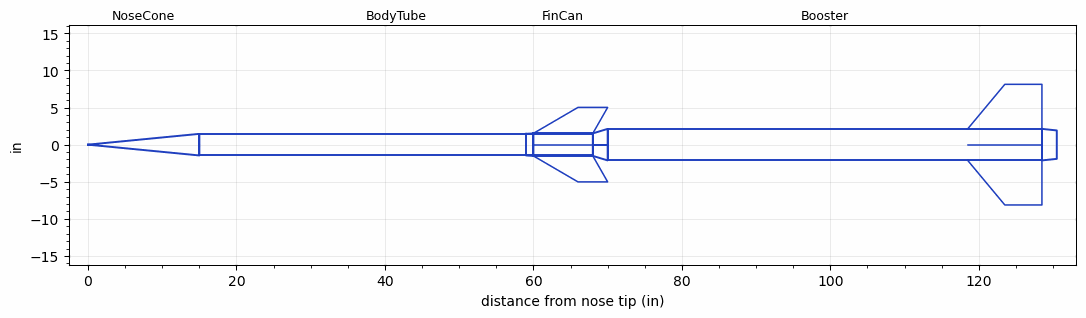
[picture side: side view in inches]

<RASAeroDocument>
 <FileVersion>2</FileVersion>
 <RocketDesign>
  <NoseCone>
   <Length>15</Length>
   <Diameter>2.91</Diameter>
   <Shape>Conical</Shape>
   <BluntRadius>0.1</BluntRadius>
   <Location>0</Location>
  </NoseCone>
  <BodyTube>
   <Length>53</Length>
   <Diameter>2.91</Diameter>
   <Location>15</Location>
   <Protuberance>
    <StreamlinedNoBaseDrag>0</StreamlinedNoBaseDrag>
    <StreamlinedWithBaseDrag>0.65</StreamlinedWithBaseDrag>
    <InclinedPlate1Angle>0</InclinedPlate1Angle>
    <InclinedPlate1FrontalArea>0</InclinedPlate1FrontalArea>
    <InclinedPlate2Angle>0</InclinedPlate2Angle>
    <InclinedPlate2FrontalArea>0</InclinedPlate2FrontalArea>
   </Protuberance>
  </BodyTube>
  <FinCan>
   <Length>8</Length>
   <Diameter>3.035</Diameter>
   <InsideDiameter>2.91</InsideDiameter>
   <Location>68</Location>
   <ShoulderLength>1</ShoulderLength>
   <Offset>-8</Offset>
   <Fin>
    <Count>4</Count>
    <Chord>8</Chord>
    <Span>3.5</Span>
    <SweepDistance>6</SweepDistance>
    <TipChord>4</TipChord>
    <Thickness>0.187</Thickness>
    <LERadius>0.01</LERadius>
    <Location>8</Location>
    <AirfoilSection>Hexagonal</AirfoilSection>
    <FX1>0.75</FX1>
    <FX3>0.75</FX3>
   </Fin>
  </FinCan>
  <Booster>
   <Length>58.5</Length>
   <Diameter>4.25</Diameter>
   <InsideDiameter>3.035</InsideDiameter>
   <RailGuideDiameter>0.7</RailGuideDiameter>
   <RailGuideHeight>0.6</RailGuideHeight>
   <Location>68</Location>
   <ShoulderLength>2</ShoulderLength>
   <BoattailLength>2</BoattailLength>
   <BoattailRearDiameter>3.828</BoattailRearDiameter>
   <Fin>
    <Count>4</Count>
    <Chord>10</Chord>
    <Span>6</Span>
    <SweepDistance>5</SweepDistance>
    <TipChord>5</TipChord>
    <Thickness>0.187</Thickness>
    <LERadius>0.01</LERadius>
    <Location>10</Location>
    <AirfoilSection>Hexagonal</AirfoilSection>
    <FX1>0.75</FX1>
    <FX3>0.75</FX3>
   </Fin>
   <Protuberance>
    <StreamlinedNoBaseDrag>0</StreamlinedNoBaseDrag>
    <StreamlinedWithBaseDrag>0</StreamlinedWithBaseDrag>
    <InclinedPlate1Angle>40</InclinedPlate1Angle>
    <InclinedPlate1FrontalArea>0.65</InclinedPlate1FrontalArea>
    <InclinedPlate2Angle>0</InclinedPlate2Angle>
    <InclinedPlate2FrontalArea>0</InclinedPlate2FrontalArea>
   </Protuberance>
  </Booster>
  <Surface>Rough Camouflage Paint</Surface>
  <ModifiedBarrowman>True</ModifiedBarrowman>
  <Turbulence>True</Turbulence>
  <UseBooster1>False</UseBooster1>
  <UseBooster2>False</UseBooster2>
 </RocketDesign>
 <LaunchSite>
  <Altitude>3700</Altitude>
  <Pressure>30</Pressure>
  <RodAngle>5</RodAngle>
  <RodLength>20</RodLength>
  <Temperature>80</Temperature>
  <WindSpeed>5</WindSpeed>
 </LaunchSite>
 <Recovery>
  <Altitude1>1000</Altitude1>
  <Altitude2>3000</Altitude2>
  <DeviceType1>Parachute</DeviceType1>
  <DeviceType2>Parachute</DeviceType2>
  <Event1>True</Event1>
  <Event2>True</Event2>
  <Size1>12</Size1>
  <Size2>36</Size2>
  <EventType1>Apogee</EventType1>
  <EventType2>Altitude</EventType2>
  <CD1>1</CD1>
  <CD2>1.5</CD2>
 </Recovery>
 <SimulationList>
  <Simulation>
   <SustainerEngine>N3364  (TsKrush)</SustainerEngine>
   <SustainerLaunchWt>19.1</SustainerLaunchWt>
   <SustainerNozzleDiameter>2.5</SustainerNozzleDiameter>
   <SustainerCG>40</SustainerCG>
   <SustainerIgnitionDelay>10</SustainerIgnitionDelay>
   <Booster1Engine>O8220  (O8220)</Booster1Engine>
   <Booster1LaunchWt>71.1</Booster1LaunchWt>
   <Booster1SeparationDelay>0</Booster1SeparationDelay>
   <Booster1IgnitionDelay>0</Booster1IgnitionDelay>
   <Booster1CG>70.2</Booster1CG>
   <Booster1NozzleDiameter>3.75</Booster1NozzleDiameter>
   <IncludeBooster1>True</IncludeBooster1>
   <Booster2Delay>0</Booster2Delay>
   <IncludeBooster2>False</IncludeBooster2>
   <TimetoApogee>175.6546</TimetoApogee>
   <MaxAltitude>448419.3</MaxAltitude>
   <MaxVelocity>6597.353</MaxVelocity>
  </Simulation>
 </SimulationList>
</RASAeroDocument>
